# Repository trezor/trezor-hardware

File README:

Hardware design of TREZOR

https://trezor.io/

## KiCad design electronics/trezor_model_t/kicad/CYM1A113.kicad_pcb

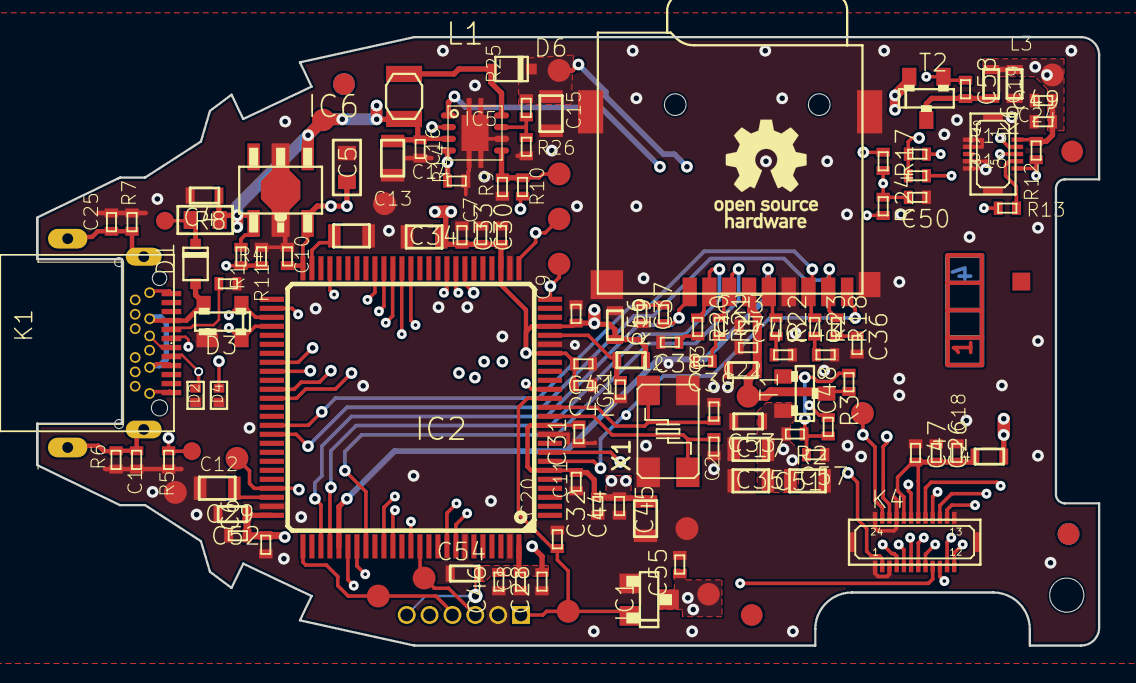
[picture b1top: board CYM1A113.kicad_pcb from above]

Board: 4 copper layers, 59.0 x 33.8 mm, 132 parts (0 on the bottom side), 71 nets.

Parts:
@HOLE0: (no value)
C1, C11, C25, C33, C46, C58: 1n; 0402
C2, C3: 22p; 0402
C4, C19, C22, C52, C53, C54, C56: 1u; 0603_REFLOW
C5: 1u; 0603
C6, C8, C23, C30, C32, C42, C47, C49: 10n; 0402
C7, C9, C10, C16, C18, C20, C21, C24, C26, C27, C28, C29, C31, C41, C44, C48, C55: 100n; 0402
C12, C13, C17, C34, C35, C45, C51: 2u2; 0805_REFLOW
C14, C15: 4u7/16V; 0805_REFLOW
C36, C37, C38, C39, C40, C43: 47p; 0402
C50, C57: 220p; 0402
D1: PMEG3005; SOD323F
D2, D4: PESD5V0F1BLD; SOD882D
D3: PRTR5V0U2X; SOT143B_REFLOW
D6: PMEG4005; SOD323F
IC1: MIC803-29D2VC3; SOT23_MEDIUM_SIZE
IC2: STM32F427VIT6; LQFP100_NO_CENTER_NO_TDOCU
IC5: TPS61043; WSON-8_3X3MM
IC6: XC6210B332PR; SOT89-5
K1: DX07B024XJ1R1300; USB_C_JAE_DX07B024XJ1
K3: ATTEND_112J-TDAR-R01; ATTEND_112J-TXAR-R01_SMALL
K4: DF37NB-24DS-0.4V
K5: SWD
K6: DF37NB-10DS-0.4V
L1: 4u7 VLS252008ET-4R7M; L_2.5X2.0
L2, L3, L4: BLM18AG102SN1D; 0603_REFLOW
R1: 22R; 0402
R2, R17: 470k; 0402
R3, R24: 22k; 0402
R4, R5: 5k1; 0402
R6, R7: 1M; 0402
R8: MF-FSMF020X-2; 0603
R9: 330R; 0402
R10, R18, R19, R20, R21, R22, R23: 68R; 0402
R11, R26: N.C.; 0402
R12: 10k; 0402
R13: 100R; 0402
R14: 27R; 0402
R15, R16: 1k5; 0402
R25: 0R; 0402
T1, T2: DMP2045U; SOT23_REFLOW
TP1, TP2, TP4, TP6, TP7, TP8, TP9, TP12, TP13, TP14, TP15, TP16: MB_1.27; MB1.27
TP3, TP5, TP10, TP11: MB_1.50; MB1.5
TP19, TP20: MB_1.00
U$45, U$46, U$48, U$49, U$56, U$57: CENTR
U$47: BADMARK
U$54: LAYER_STACK_4_LAYERS
X1: CTS406 8MHz; X6,0X3,5

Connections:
/CC1: K1.A5, R4.P$2
/CC2: R5.P$2, TP20.1
/DN: D3.3, IC2.53, K1.A7, K1.B7
/DP: D3.2, IC2.54, K1.A6, K1.B6
/HS_VBUS: IC2.52, R1.P$1, R11.P$1
/LEDA: C15.2, D6.K, K4.22, R25.P$1, TP7.1
/LEDK: IC5.1, K4.23, TP4.1
/MCU_EINT: IC2.33, R13.P$2
/PWM: IC2.32, R10.P$1
/REST: IC2.34, K6.5, R12.P$2
/SBU1: D2.2, IC2.25, TP10.1
/SBU2: D4.2, IC2.26, TP11.1
/SD_ON: IC2.15, R3.P$1
/TOUCH_ON: IC2.47, R24.P$2
/VBUS: D1.A, D3.4, K1.A4, K1.B9
GND: C1.P$1, C2.P$1, C3.P$1, C4.1, C5.1, C6.P$1, C7.P$1, C8.P$1, C9.P$1, C10.P$1, C11.P$1, C12.1, C13.1, C14.2, C15.1, C16.P$1, C17.1, C18.P$1, C19.1, C20.P$1, C21.P$1, C22.1, C23.P$1, C24.P$1, C25.P$1, C26.P$1, C27.P$1, C28.P$1, C29.P$1, C30.P$1, C31.P$1, C32.P$1, C33.P$1, C34.1, C35.1, C36.P$2, C37.P$2, C38.P$2, C39.P$2, C40.P$2, C41.P$1, C42.P$1, C43.P$2, C44.P$1, C45.1, C46.P$1, C47.P$1, C49.P$1, C50.P$1, C51.1, C52.1, C53.1, C54.2, C55.P$2, C56.2, C57.P$1, D2.1, D3.1, D4.1, IC1.1, IC2.10, IC2.20, IC2.27, IC2.74, IC2.94, IC2.99, IC5.6, IC5.EP, IC5.EP$1, IC5.EP$2, IC5.EP$3, IC5.EP$4, IC6.2, K3.6, K3.GND@1, K3.GND@2, K3.GND@3, K3.GND@4, K4.1, K4.3, K4.13, K4.21, K4.24, K4.25, K4.26, K5.GND, K6.6, K6.7, K6.9, K6.10, K6.11, K6.12, R4.P$1, R5.P$1, R6.P$1, R7.P$1, R9.P$1, R11.P$2, R14.P$1, R26.P$2, TP9.1, TP12.1, TP13.1, X1.2, X1.4
unnamed: C1.P$2, R6.P$2
unnamed: C2.P$2, IC2.12, X1.1
unnamed: C3.P$2, IC2.13, X1.3
unnamed: C12.2, IC2.73
unnamed: C13.2, IC2.49
unnamed: C18.P$2, C26.P$2, C47.P$2, K4.18, K4.20, L4.1
unnamed: C20.P$2, IC1.2, IC2.14, K5.RST, TP14.1
unnamed: C21.P$2, IC2.21, L2.2
unnamed: C22.2, C23.P$2, C27.P$2, C48.P$1, K3.4, T1.3, TP15.1
unnamed: C25.P$2, K1.SH1, K1.SH2, R7.P$2
unnamed: C36.P$1, R18.P$2
unnamed: C37.P$1, R19.P$2
unnamed: C38.P$1, R20.P$2
unnamed: C39.P$1, R21.P$2
unnamed: C40.P$1, R22.P$2
unnamed: C43.P$1, R23.P$2
unnamed: C48.P$2, C57.P$2, R2.P$1, R3.P$2, T1.2
unnamed: C50.P$2, C58.P$1, R17.P$2, R24.P$1, T2.2
unnamed: C58.P$2, L3.1, T2.3
unnamed: D1.K, R8.2, TP19.1
unnamed: D6.A, IC5.8, L1.2
unnamed: IC2.7, K3.CD
unnamed: IC2.8, K4.2
unnamed: IC2.38, K4.8
unnamed: IC2.39, K4.7
unnamed: IC2.40, K4.6
unnamed: IC2.41, K4.5
unnamed: IC2.42, K4.4
unnamed: IC2.58, K4.16
unnamed: IC2.59, K4.19
unnamed: IC2.61, K4.12
unnamed: IC2.62, K4.11
unnamed: IC2.65, K3.7, R23.P$1
unnamed: IC2.66, K3.8, R18.P$1
unnamed: IC2.72, K5.SWDIO, TP1.1
unnamed: IC2.76, K5.SWCLK, TP2.1
unnamed: IC2.78, K3.1, R19.P$1
unnamed: IC2.79, K3.2, R20.P$1
unnamed: IC2.80, K3.5, R22.P$1
unnamed: IC2.81, K4.10
unnamed: IC2.82, K4.9
unnamed: IC2.83, K3.3, R21.P$1
unnamed: IC2.85, K4.14
unnamed: IC2.86, K4.15
unnamed: IC2.88, K4.17
unnamed: IC2.89, K5.SWO, TP8.1
unnamed: IC2.92, K6.2, R15.P$1
unnamed: IC2.93, K6.3, R16.P$1
unnamed: IC5.2, IC5.4, R14.P$2
unnamed: IC5.5, R9.P$2, R10.P$2, TP6.1
unnamed: IC5.7, R25.P$2, R26.P$1
unnamed: K6.4, R13.P$1
VBAT: C19.2, C24.P$2, C49.P$2, K6.1, L3.2, R12.P$1, R15.P$2, R16.P$2, TP16.1
VCC: C4.2, C14.1, C16.P$2, IC5.3, IC6.1, IC6.4, L1.1, R1.P$2, R8.1, TP5.1
VCC-2: C5.2, C6.P$2, C7.P$2, C8.P$2, C9.P$2, C10.P$2, C11.P$2, C17.2, C28.P$2, C29.P$2, C30.P$2, C31.P$2, C32.P$2, C33.P$2, C34.2, C35.2, C41.P$2, C42.P$2, C44.P$2, C45.2, C46.P$2, C51.2, C52.2, C53.2, C54.1, C55.P$1, C56.1, IC1.3, IC2.6, IC2.11, IC2.19, IC2.22, IC2.28, IC2.50, IC2.75, IC2.100, IC6.5, K5.VCC, L2.1, L4.2, R2.P$2, R17.P$1, T1.1, T2.1, TP3.1

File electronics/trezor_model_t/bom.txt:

Part Value                Device                                  Package
C1   1n/50V               C_0402                                  0402
C2   22p                  C_0402                                  0402
C3   22p                  C_0402                                  0402
C4   1u                   C_0603                                  0603
C5   1u                   C_0603                                  0603
C6   10n                  C_0402                                  0402
C7   100n                 C_0402                                  0402
C8   10n                  C_0402                                  0402
C9   100n                 C_0402                                  0402
C10  100n                 C_0402                                  0402
C11  1n                   C_0402                                  0402
C12  2u2                  C_0805                                  0805
C13  2u2                  C_0805                                  0805
C14  4u7/16V              C_0805                                  0805
C15  4u7/16V              C_0805                                  0805
C16  100n                 C_0402                                  0402
C17  2u2                  C_0805                                  0805
C18  100n                 C_0402                                  0402
C19  1u                   C_0603                                  0603
C20  100n                 C_0402                                  0402
C21  100n                 C_0402                                  0402
C22  1u                   C_0603                                  0603
C23  10n                  C_0402                                  0402
C24  100n                 C_0402                                  0402
C25  1n/50V               C_0402                                  0402
C26  100n                 C_0402                                  0402
C27  100n                 C_0402                                  0402
C28  100n                 C_0402                                  0402
C29  100n                 C_0402                                  0402
C30  10n                  C_0402                                  0402
C31  100n                 C_0402                                  0402
C32  10n                  C_0402                                  0402
C33  1n                   C_0402                                  0402
C34  2u2                  C_0805                                  0805
C35  2u2                  C_0805                                  0805
C36  47p                  C_0402                                  0402
C37  47p                  C_0402                                  0402
C38  47p                  C_0402                                  0402
C39  47p                  C_0402                                  0402
C40  47p                  C_0402                                  0402
C41  100n                 C_0402                                  0402
C42  10n                  C_0402                                  0402
C43  47p                  C_0402                                  0402
C44  100n                 C_0402                                  0402
C45  2u2                  C_0805                                  0805
C46  1n                   C_0402                                  0402
C47  10n                  C_0402                                  0402
C48  100n                 C_0402                                  0402
C49  10n                  C_0402                                  0402
C50  220p                 C_0402                                  0402
C51  2u2                  C_0805                                  0805
C52  1u                   C_0603                                  0603
C53  1u                   C_0603                                  0603
C54  1u                   C_0603                                  0603
C55  100n                 C_0402                                  0402
C56  1u                   C_0603                                  0603
C57  220p                 C_0402                                  0402
C58  1n                   C_0402                                  0402
D1   PMEG3005EJ           DS_SOD323F                              SOD323F
D2   PESD5V0F1BLD         D_TRANSIL_BI_SOD882D                    SOD882D
D3   PRTR5V0U2X           PRTR5V0_SOT143B                         SOT143B
D4   PESD5V0F1BLD         D_TRANSIL_BI_SOD882D                    SOD882D
D6   PMEG4005EJ           DS_SOD323F                              SOD323F
IC1  MIC803-30D2VC3                                               SC70-3
IC2  STM32F427VIT6        STM32F427_LQFP100                       LQFP100_NO_CENTER_NO_TDOCU
IC5  TPS61043             TP6104X_WSON-8_3X3MM                    WSON-8_3X3MM
IC6  XC6210B332PR         XC6210B_SOT89-5                         SOT89-5
K1   DX07B024XJ1R1300     USB-C_JAE_DX07B024XJ1                   USB_C_JAE_DX07B024XJ1
K3   ATTEND_112J-TDAR-R01 KON_µSD_CARD_ATTEND_112J_TXAR_R01_SMALL ATTEND_112J-TXAR-R01_SMALL
K4   DF37NB-24DS-0.4V     DISPLEJ_154A2411CTP01                   DF37NB-24DS-0.4V
K5   SWD                  SWD                                     SWD
K6   DF37NB-10DS-0.4V     DISPLEJ_154A2411CTP01_TOUCH             DF37NB-10DS-0.4V
L1   4u7 VLS252008ET-4R7M L_2.5X2.0                               L_2.5X2.0
L2   BLM18AG601SN1D       L_0603                                  0603
L3   BLM18AG601SN1D       L_0603                                  0603
L4   BLM18AG601SN1D       L_0603                                  0603
LCD1                      LCD_DISPLEJ                             LCD
R1   22R                  R_0402                                  0402
R2   470k                 R_0402                                  0402
R3   22k                  R_0402                                  0402
R4   5k1                  R_0402                                  0402
R5   5k1                  R_0402                                  0402
R6   1M                   R_0402                                  0402
R7   1M                   R_0402                                  0402
R8   MF-FSMF020X-2        POLYSWITCH_0603                         0603
R9   330R                 R_0402                                  0402
R10  68R                  R_0402                                  0402
R11  N.C.                 R_0402                                  0402
R12  10k                  R_0402                                  0402
R13  100R                 R_0402                                  0402
R14  27R                  R_0402                                  0402
R15  1k5                  R_0402                                  0402
R16  1k5                  R_0402                                  0402
R17  470k                 R_0402                                  0402
R18  68R                  R_0402                                  0402
R19  68R                  R_0402                                  0402
R20  68R                  R_0402                                  0402
R21  68R                  R_0402                                  0402
R22  68R                  R_0402                                  0402
R23  68R                  R_0402                                  0402
R24  22k                  R_0402                                  0402
R25  0R                   R_0402                                  0402
R26  N.C.                 R_0402                                  0402
T1   DMP2045U                                                     SOT-23
T2   DMP2045U                                                     SOT-23
X1   CTS406 8MHz          X_4V_6,0X3,5                            X6,0X3,5

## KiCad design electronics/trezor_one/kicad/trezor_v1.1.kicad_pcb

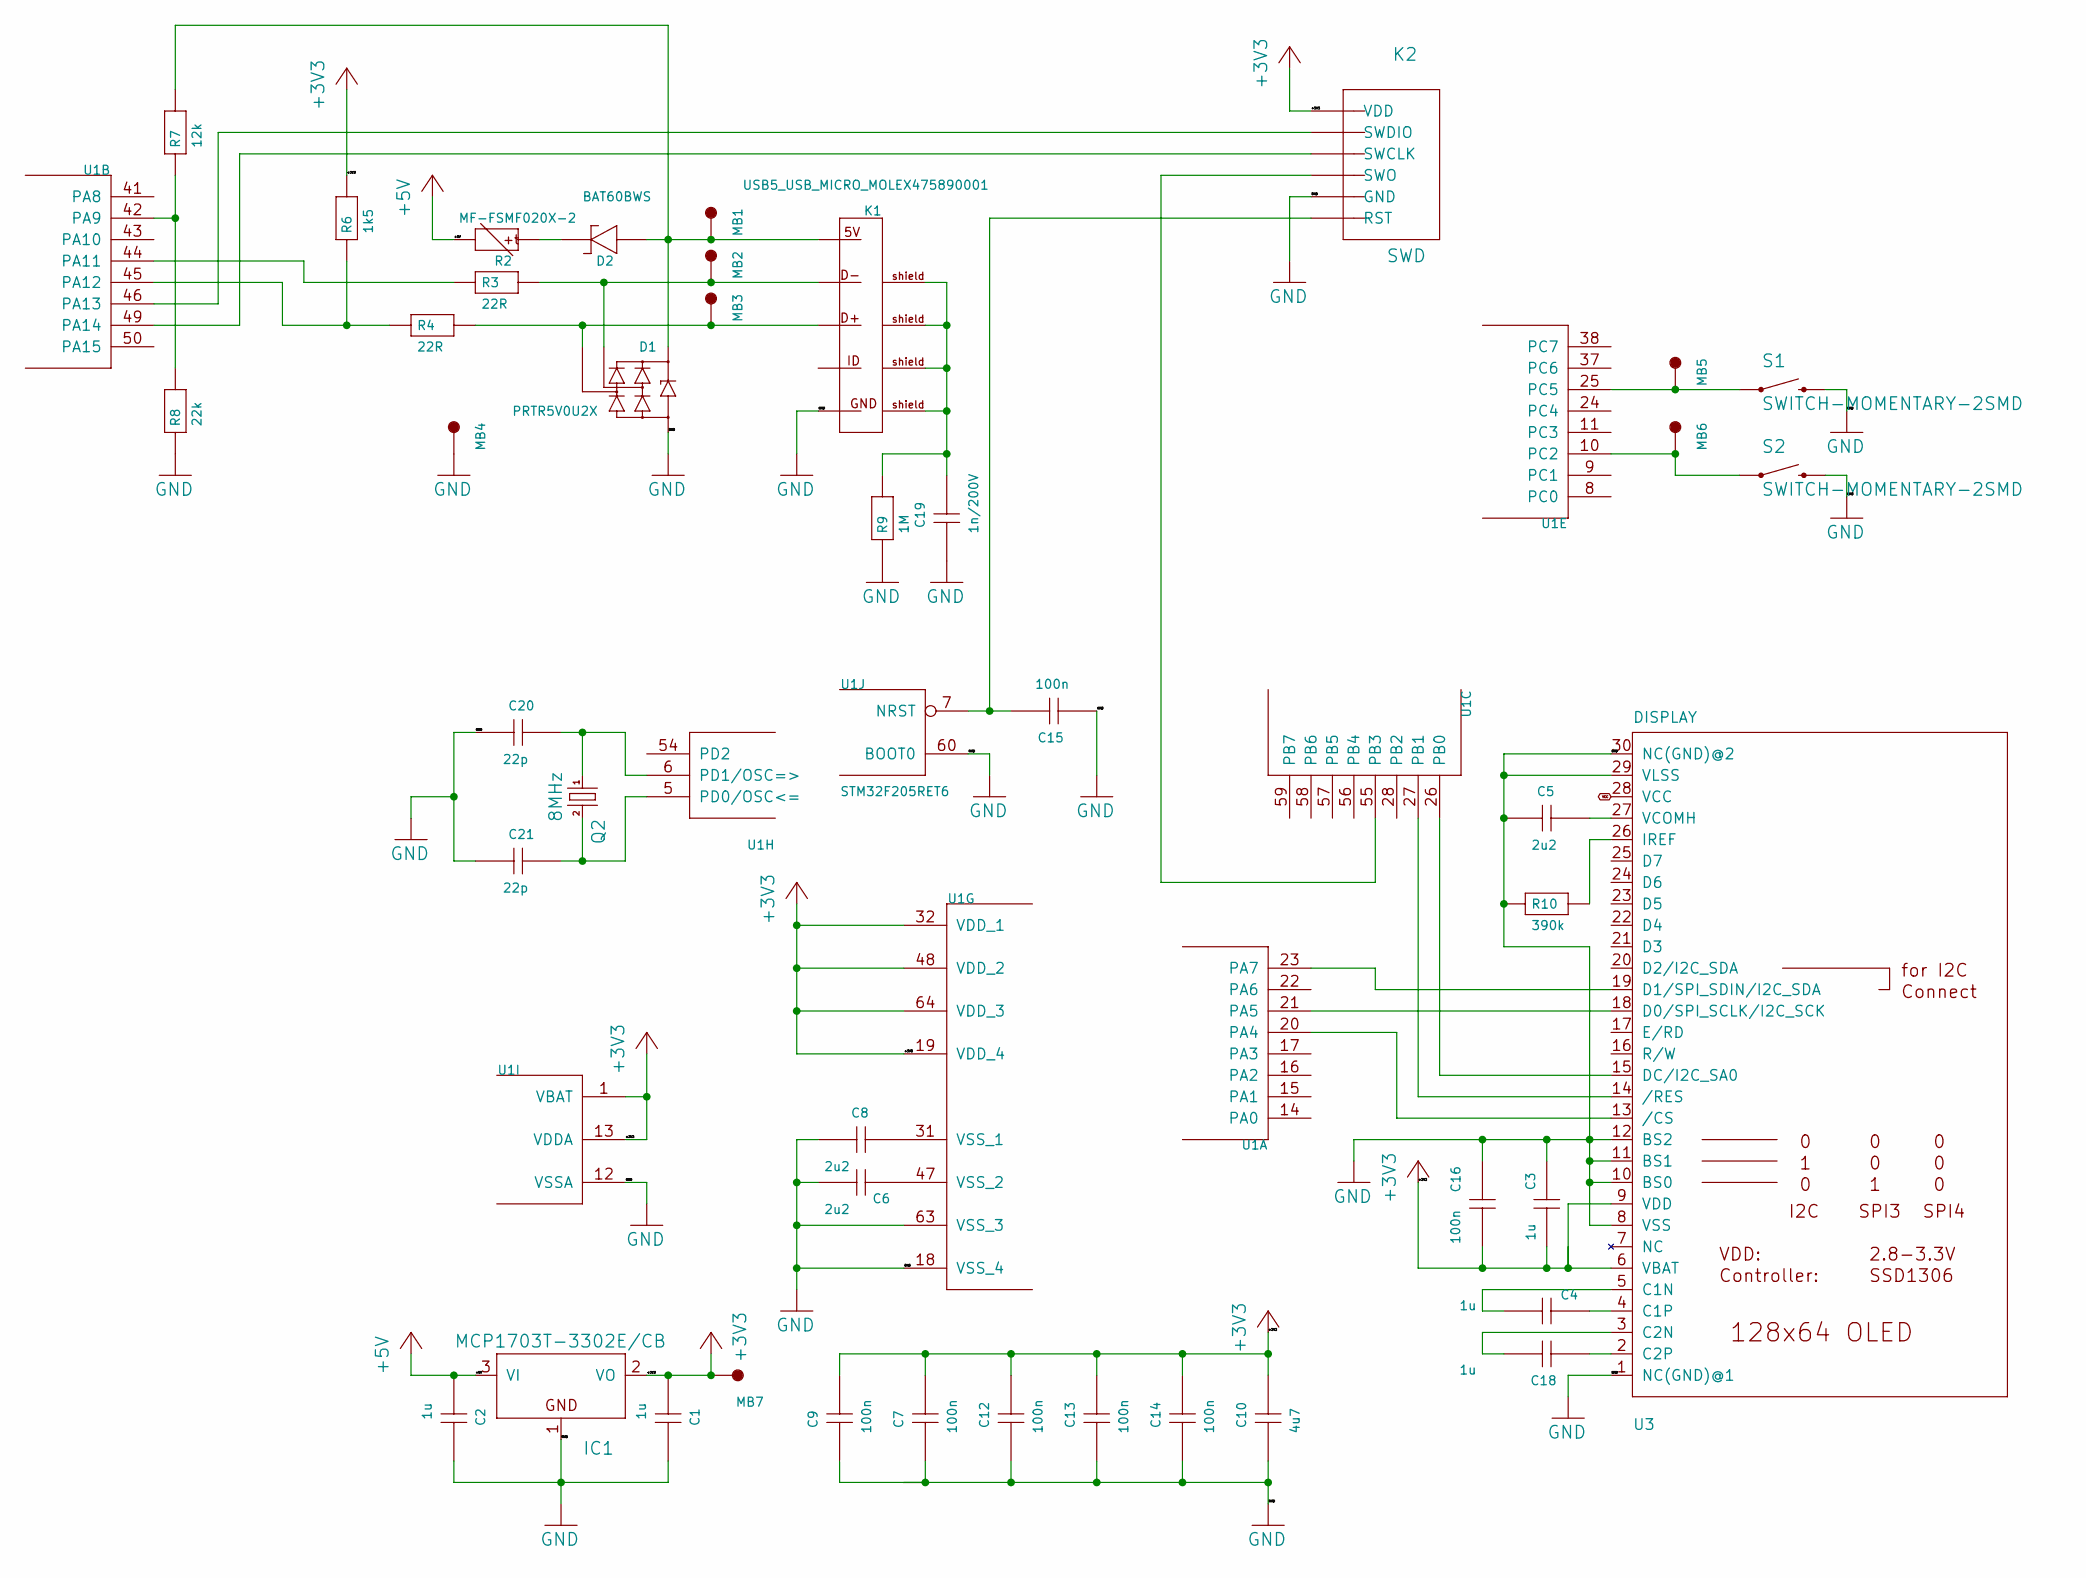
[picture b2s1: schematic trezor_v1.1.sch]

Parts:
C1, C2, C3, C4, C18: 1u; 0402
C5: 2u2; 0603
C6, C8: 2u2; 0402
C7, C9, C12, C13, C14, C15, C16: 100n; 0402
C10: 4u7; 0603
C19: 1n/200V; 0603
C20, C21: 22p; 0402
D1: PRTR5V0U2X; SOT143B
D2: BAT60BWS; SOD323
IC1: MCP1703T-3302E/CB; SOT23
K1: USB5_USB_MICRO_MOLEX475890001; USB_MICRO-MOLEX475890001
K2: SWD
MB1, MB2, MB3, MB4, MB5, MB6, MB7: MB_1.50; MB1.5
Q2: 8MHz; CTS406
R2: MF-FSMF020X-2; 0603
R3, R4: 22R; 0402
R6: 1k5; 0402
R7: 12k; 0402
R8: 22k; 0402
R9: 1M; 0603
R10: 390k; 0402
S1, S2: SWITCH-MOMENTARY-2SMD; TACTILE_SWITCH_SMD
U1: STM32F205RET6; TQFP64
U3: DISPLAY; UG-2864HSWEG01_0.96IN_WRAPAROUND

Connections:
+3V3: C1.P$1 (1), C3.P$1 (1), C7.P$2 (2), C9.P$2 (2), C10.2, C12.P$2 (2), C13.P$2 (2), C14.P$2 (2), C16.P$1 (1), IC1.2 (VO), K2.6 (VDD), MB7.1, R6.P$2 (2), U1.1 (VBAT), U1.13 (VDDA), U1.19 (VDD_4), U1.32 (VDD_1), U1.48 (VDD_2), U1.64 (VDD_3), U3.6 (VBAT), U3.9 (VDD)
+5V: C2.P$1 (1), IC1.3 (VI), R2.2
GND: C1.P$2 (2), C2.P$2 (2), C3.P$2 (2), C5.1, C6.P$1 (1), C7.P$1 (1), C8.P$1 (1), C9.P$1 (1), C10.1, C12.P$1 (1), C13.P$1 (1), C14.P$1 (1), C15.P$1 (1), C16.P$2 (2), C19.1, C20.P$1 (1), C21.P$1 (1), D1.1 (GND), IC1.1 (GND), K1.5 (5_GND), K2.2 (GND), MB4.1, R8.P$1 (1), R9.1, R10.P$1 (1), S1.3 (2), S1.4 (2), S2.3 (2), S2.4 (2), U1.12 (VSSA), U1.18 (VSS_4), U1.60 (BOOT0), U1.63 (VSS_3), U3.1 (NC(GND)@1), U3.8 (VSS), U3.10 (BS0), U3.11 (BS1), U3.12 (BS2), U3.29 (VLSS), U3.30 (NC(GND)@2)
unnamed: C4.P$1 (1), U3.4 (C1P)
unnamed: C4.P$2 (2), U3.5 (C1N)
unnamed: C5.2, U3.27 (VCOMH)
unnamed: C6.P$2 (2), U1.47 (VSS_2)
unnamed: C8.P$2 (2), U1.31 (VSS_1)
unnamed: C15.P$2 (2), K2.1 (RST), U1.7 (NRST)
unnamed: C18.P$1 (1), U3.2 (C2P)
unnamed: C18.P$2 (2), U3.3 (C2N)
unnamed: C19.2, K1.S1_BOT (SHIELD_1), K1.S1_TOP (SHIELD_1), K1.S2_BOT (SHIELD_2), K1.S2_TOP (SHIELD_2), K1.S3_BOT (SHIELD_3), K1.S3_TOP (SHIELD_3), K1.S4_BOT (SHIELD_4), K1.S4_TOP (SHIELD_4), K1.SA (SHIELD_1), K1.SB (SHIELD_2), R9.2
unnamed: C20.P$2 (2), Q2.1, U1.6 (PD1/OSC=>)
unnamed: C21.P$2 (2), Q2.3 (2), U1.5 (PD0/OSC<=)
unnamed: D1.2 (I/O1), K1.2 (2_D-), MB2.1, R3.P$2 (2)
unnamed: D1.3 (I/O2), K1.3 (3_D+), MB3.1, R4.P$2 (2)
unnamed: D1.4 (VCC), D2.A (1), K1.1 (1_5V), MB1.1, R7.P$2 (2)
unnamed: D2.K (2), R2.1
unnamed: K2.3 (SWO), U1.55 (PB3)
unnamed: K2.4 (SWCLK), U1.49 (PA14)
unnamed: K2.5 (SWDIO), U1.46 (PA13)
unnamed: MB5.1, S1.1, S1.2 (1), U1.25 (PC5)
unnamed: MB6.1, S2.1, S2.2 (1), U1.10 (PC2)
unnamed: R3.P$1 (1), U1.44 (PA11)
unnamed: R4.P$1 (1), R6.P$1 (1), U1.45 (PA12)
unnamed: R7.P$1 (1), R8.P$2 (2), U1.42 (PA9)
unnamed: R10.P$2 (2), U3.26 (IREF)
unnamed: U1.20 (PA4), U3.13 (/CS)
unnamed: U1.21 (PA5), U3.18 (D0/SPI_SCLK/I2C_SCK)
unnamed: U1.23 (PA7), U3.19 (D1/SPI_SDIN/I2C_SDA)
unnamed: U1.26 (PB0), U3.15 (DC/I2C_SA0)
unnamed: U1.27 (PB1), U3.14 (/RES)
VCC: U3.28 (VCC)

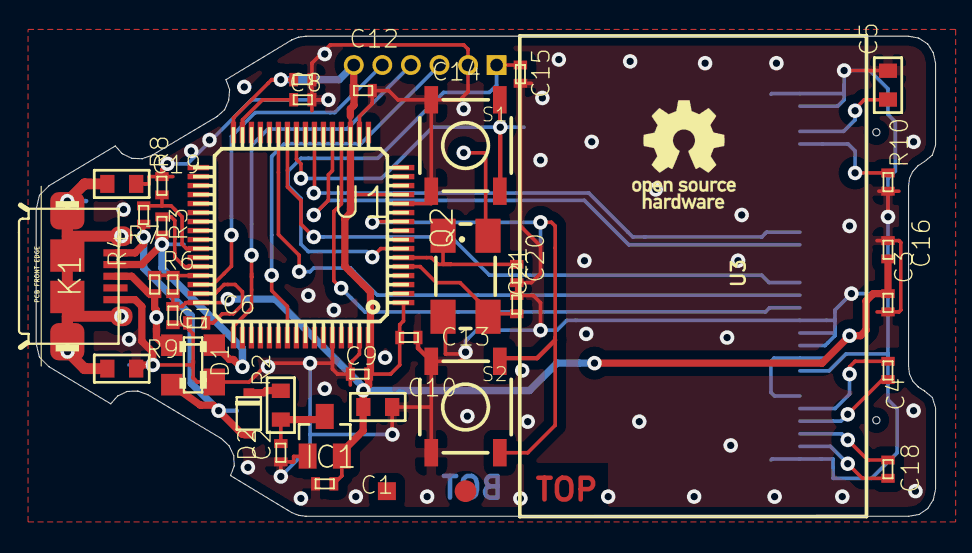
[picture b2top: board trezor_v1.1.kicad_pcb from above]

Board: 16 copper layers, 50.0 x 26.7 mm, 46 parts (0 on the bottom side), 32 nets.

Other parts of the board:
U$3: BADMARK
U$4: CENTR

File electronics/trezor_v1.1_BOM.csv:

Qty,Value,Device,Package,Parts,Description
7,100n,C_0402,402,"C7, C9, C12, C13, C14, C15, C16",
1,12k,R_0402,402,R7,
1,1M,R_0603,603,R9,
1,1k5,R_0402,402,R6,
1,1n/200V,C_0603,603,C19,
5,1u,C_0402,402,"C1, C2, C3, C4, C18",
2,22R,R_0402,402,"R3, R4",
1,22k,R_0402,402,R8,
2,22p,C_0402,402,"C20, C21",
2,2u2,C_0402,402,"C6, C8",
1,2u2,C_0603,603,C5,
1,390k,R_0402,402,R10,
1,4u7,C_0603,603,C10,
1,8MHz,CRYSTALCTS406,CTS406,Q2,CRYSTAL
1,BAT60BWS,DS_SOD323,SOD323,D2,
1,DISPLAY,"DISP_OLED_UG-2864HSWEG010.96"";UG-2864HSWEG01_0.96IN_WRAPAROUND""",U3,UG-2864HSWEG01 OLED display,
1,MCP1703T-3302E/CB,MCP1703CB,SOT23,IC1,"250 mA, 16V, Low Quiescent Current LDO Regulator"
1,MF-FSMF020X-2 ,POLYSWITCH_0603,603,R2,
1,PRTR5V0U2X,PRTR5V0_SOT143B,SOT143B,D1,
1,STM32F205RET6,STM32F10XRXT6,TQFP64,U1,STM32F101/103 64pin LQFP
1,SWD,SWD,SWD,K2,SWD
2,SWITCH-MOMENTARY-2SMD,SWITCH-MOMENTARY-2SMD,TACTILE_SWITCH_SMD,"S1, S2","Various NO switches- pushbuttons, reed, etc"
1,USB5_USB_MICRO_MOLEX475890001,USB5_USB_MICRO_MOLEX475890001,USB_MICRO-MOLEX475890001,K1,

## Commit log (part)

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2012-11-09 init code
2012-11-09 fix distance for display
2012-11-13 rework raspi board
2012-11-13 add gnd polygons
2012-11-13 printing preparations
2012-11-29 add new stls
2013-01-10 work on shield
2013-01-14 work in progress
2013-01-21 work on product scheme
2013-02-03 work on pcbs
2013-02-07 try freerouting
2013-02-07 routed
2013-02-14 new pcb size :-/
2013-02-21 raspi shield
2013-02-21 work on product
2013-02-24 raspi work rename product to trezor
2013-02-25 work snapshot
2013-02-25 forgot to connect usb gnd/vcc
2013-03-09 work on raspi
2013-03-11 work on rpi
2013-03-18 raspi work
2013-03-24 rework BOMs
2013-03-24 logo tDocu->tSilk
2013-03-24 add pinheader
2013-03-25 raspi
2013-04-01 rework to STM32 (WIP)
2013-04-08 trezor WIP
2013-04-08 revert dimension change
2013-04-08 remove unused files
2013-04-08 add url
2013-04-09 move capacitors to the edge
2013-04-12 add items to trezor bom
2013-04-12 fix typo in trezor bom
2013-04-12 align boms
2013-04-15 connect vbus to mcu as well
2013-04-19 programmer
2013-04-24 rework swd programmer
2013-05-02 add farnell links
2013-05-03 fix unconnected pin
2013-06-25 change crystal
2013-07-23 repository cleanup
2014-02-26 add bitmaps
2014-05-28 change capacitor
2015-10-14 add board photo
2015-10-15 cleanup eagle filenames (trezor -> trezor_v1.0, trezor_v1 -> trezor_v1.1)
2016-05-06 add two forgotten missing files about programmer
2016-06-08 STL Models optimized for 3D Printing
2016-10-05 add png export from eagle for programmer and raspi
2017-01-10 -> trezor.io
2017-04-13 use markdown for readme
2017-06-22 add production tools (hidtest)
2017-06-23 production: refactor hidtest
2017-07-18 production: add self-test to test-trezor
2018-01-27 Added BOM for Trezor 1.1
2018-07-04 add license
2020-02-01 Fix issues with 3d printed case
    - Fix mobility of buttons
    - Reinforce lanyard connection
2020-02-01 Fix issues with 3d printed case (#9)
    - Fix mobility of buttons
    - Reinforce lanyard connection
2020-03-12 reorganize "case" folder structure
2020-06-23 Add .circleci/config.yml
2020-09-07 electronics: move Trezor One stuff to subfolder
2020-09-07 electronics: add Trezor Model T resources
2021-02-12 electronics: copy over relevant materials from trezor-firmware repo
2021-02-13 add ZIP link to README
2021-02-13 add kicad files
2021-02-16 Board edge rendering correction on kicad
2021-02-16 Fixed filled zones bug, connection issues
2021-02-16 set PCB width to 1.0 mm
2021-02-16 add CERN-OHL-S license
2021-02-16 add OSHW logo
2021-02-16 kicad import bug fixes
    fixed issues with the usb connector footprint causing kicad to be confused about the correct board edge shape
2021-02-16 add OSHW logo to Trezor One PCB
2021-02-16 add gitignore, remove extraneous kicad files
2021-02-16 remove hidtest
2021-02-16 move gitignore to root
2021-02-24 update mosfet
2021-02-24 remove obsolete T1 board
2021-11-01 add oshwa uid
2023-02-07 update sd-card board link
2023-02-09 update model t bom
2023-11-30 add Trezor Safe 3
2024-07-10 Add Trezor Safe 5 rev F
2025-10-23 Add TS7's electronics hardware designs.
2025-10-27 Slight export overlooks corrected :-)
2026-01-07 Added TS5 rev.G electronic hardware designs.
2026-01-08 Added TS5 rev.G electronic hardware designs

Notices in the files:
parts and their libraries:
microbuilder: This work is placed in the public domain, and may be freely used for commercial and non-commercial work with the following conditions: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
SparkFun-Electromechanical: Licensing: CC v3.0 Share-Alike You are welcome to use this library for commercial purposes.
